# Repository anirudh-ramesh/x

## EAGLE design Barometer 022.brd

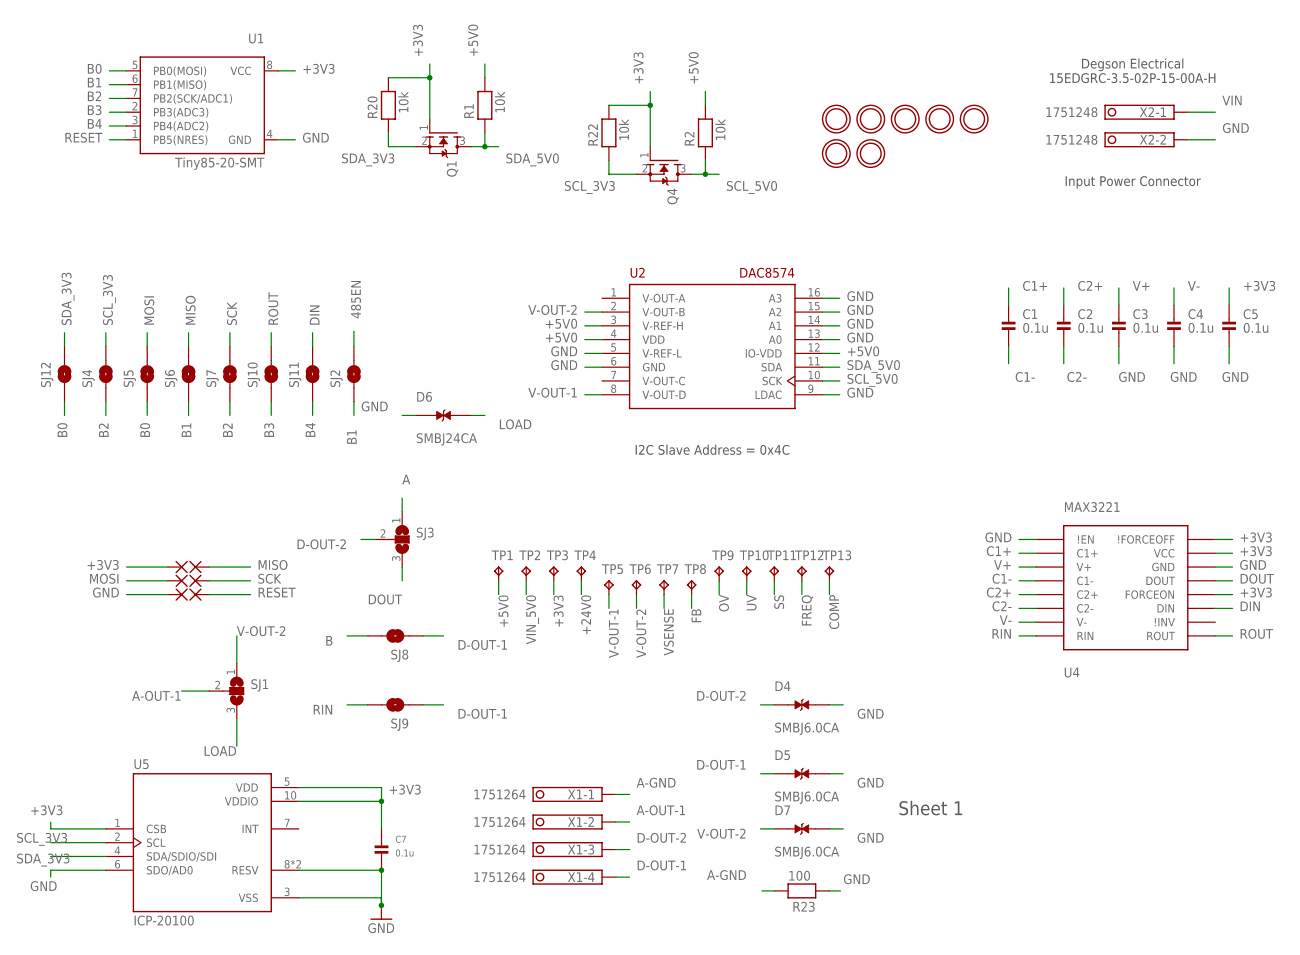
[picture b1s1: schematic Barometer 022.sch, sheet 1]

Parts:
C1, C2, C3, C4, C5, C7: 0.1u; 0603@1
D4, D5, D7: SMBJ6.0CA; DIOM4336X265N
D6: SMBJ24CA; DIOM4336X265N
PAD1, PAD2, PAD3, PAD4, PAD5, PAD6: SMD2; SMD1,27-2,54
Q1, Q4: MOSFET-NWIDE; SOT23-WIDE
R1, R2, R20, R22: 10k; 0603
R23: 100; 0603
SJ1: SJ2WW; SJ_2W
SJ2, SJ4, SJ5, SJ6, SJ7, SJ8, SJ9, SJ10, SJ11: SOLDERJUMPERTRACE; SJ_2S-TRACE
SJ3: SJ2W; SJ_2
SJ12: SOLDERJUMPERNO; SJ_2S-NO
TP1, TP2, TP3, TP4, TP5, TP6, TP7, TP8, TP9, TP10, TP11, TP12, TP13: TPB1,27; B1,27
U1: Tiny85-20-SMT; SO08-EIAJ_MCU
U2: DAC8574; TSSOP16
U4: MAX3221; TSSOP16
U5: ICP-20100; PQFN50P200X200X85-10N
U$1, U$2, U$3, U$4, U$5, U$6, U$7: MOUNTINGHOLE3.0THIN; MOUNTINGHOLE_3.0_PLATEDTHIN
X1: 1751264
X2: 1751248

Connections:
485EN: SJ2.2; also elsewhere on the board
+3V3: C5.1, C7.1, PAD1.1, Q1.1 (G), Q4.1 (G), R20.2, R22.2, TP3.TP, U1.8 (VCC), U4.12 (FORCEON), U4.15 (VCC), U4.16 (\!FORCEOFF), U5.1 (CSB), U5.5 (VDD), U5.10 (VDDIO); also elsewhere on the board
+5V0: R1.2, R2.2, TP1.TP, U2.3 (V-REF-H), U2.4 (VDD), U2.12 (IO-VDD); also elsewhere on the board
+24V0: TP4.TP; also elsewhere on the board
A: SJ3.1; also elsewhere on the board
A-GND: R23.2, X1.1
A-OUT-1: SJ1.2, X1.2
B: SJ8.2; also elsewhere on the board
B0: SJ5.1, SJ12.1, U1.5 (PB0(MOSI))
B1: SJ2.1, SJ6.1, U1.6 (PB1(MISO))
B2: SJ4.1, SJ7.1, U1.7 (PB2(SCK/ADC1))
B3: SJ10.1, U1.2 (PB3(ADC3))
B4: SJ11.1, U1.3 (PB4(ADC2))
C1+: C1.1, U4.2 (C1+)
C1-: C1.2, U4.4 (C1-)
C2+: C2.1, U4.5 (C2+)
C2-: C2.2, U4.6 (C2-)
COMP: TP13.TP; also elsewhere on the board
D-OUT-1: D5.1, SJ8.1, SJ9.1, X1.4
D-OUT-2: D4.1, SJ3.2, X1.3
DIN: SJ11.2, U4.11 (DIN); also elsewhere on the board
DOUT: SJ3.3, U4.13 (DOUT)
FB: TP8.TP; also elsewhere on the board
FREQ: TP12.TP; also elsewhere on the board
GND: C3.2, C4.2, C5.2, C7.2, D4.2, D5.2, D6.1, D7.2, PAD5.1, R23.1, U1.4 (GND), U2.5 (V-REF-L), U2.6 (GND), U2.9 (LDAC), U2.13 (A0), U2.14 (A1), U2.15 (A2), U2.16 (A3), U4.1 (\!EN), U4.14 (GND), U5.3 (VSS), U5.6 (SDO/AD0), U5.8 (RESV), U5.9 (RESV), X2.2; also elsewhere on the board
LOAD: D6.2, SJ1.3; also elsewhere on the board
MISO: PAD2.1, SJ6.2
MOSI: PAD3.1, SJ5.2
OV: TP9.TP; also elsewhere on the board
RESET: PAD6.1, U1.1 (PB5(NRES))
RIN: SJ9.2, U4.8 (RIN)
ROUT: SJ10.2, U4.9 (ROUT); also elsewhere on the board
SCK: PAD4.1, SJ7.2
SCL_3V3: Q4.2 (S), R22.1, SJ4.2, U5.2 (SCL)
SCL_5V0: Q4.3 (D), R2.1, U2.10 (SCK)
SDA_3V3: Q1.2 (S), R20.1, SJ12.2, U5.4 (SDA/SDIO/SDI)
SDA_5V0: Q1.3 (D), R1.1, U2.11 (SDA)
SS: TP11.TP; also elsewhere on the board
UV: TP10.TP; also elsewhere on the board
V+: C3.1, U4.3 (V+)
V-: C4.1, U4.7 (V-)
V-OUT-1: TP5.TP, U2.8 (V-OUT-D); also elsewhere on the board
V-OUT-2: D7.1, SJ1.1, TP6.TP, U2.2 (V-OUT-B)
VIN: X2.1; also elsewhere on the board
VIN_5V0: TP2.TP; also elsewhere on the board
VSENSE: TP7.TP; also elsewhere on the board

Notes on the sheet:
Sheet 1
I2C Slave Address = 0x4C
Input Power Connector
Degson Electrical 15EDGRC-3.5-02P-15-00A-H

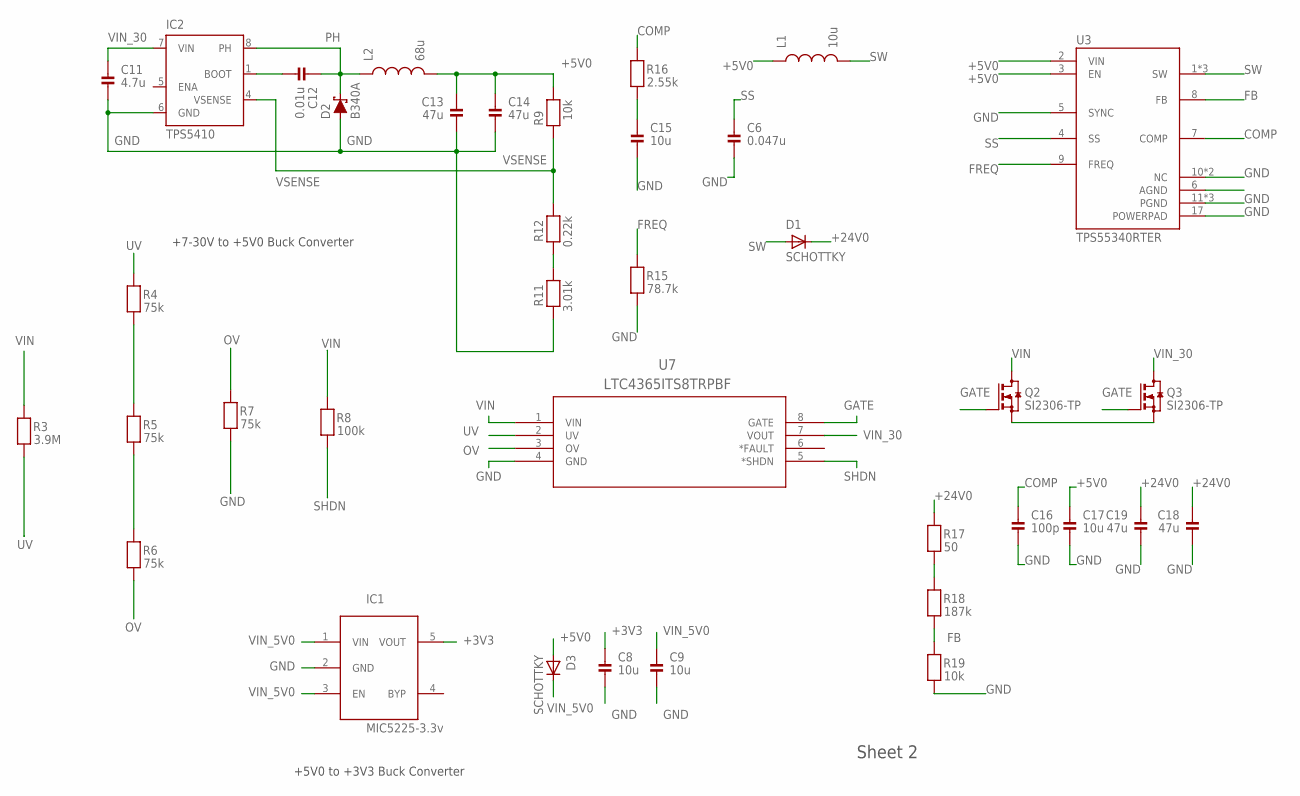
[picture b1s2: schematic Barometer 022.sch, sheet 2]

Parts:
C6: 0.047u; 0603@1
C8, C9, C15, C17: 10u; 0603@1
C11: 4.7u; 0805@1
C12: 0.01u; 0603@1
C13, C14, C18, C19: 47u; 1206@1
C16: 100p; 0603@1
D1, D3: SCHOTTKY; SOD-123FL
D2: B340A; SMA-DIODE
IC1: MIC5225-3.3v; SOT23-5L
IC2: TPS5410; D_R-PDSO-G08
L1: 10u; VLS6045EX
L2: 68u; VLS6045EX
Q2, Q3: SI2306-TP; SOT23
R3: 3.9M; 0603
R4, R5, R6, R7: 75k; 0603
R8: 100k; 0603
R9, R19: 10k; 0603
R11: 3.01k; 0603
R12: 0.22k; 0603
R15: 78.7k; 0603
R16: 2.55k; 0603
R17: 50; 0603
R18: 187k; 0603
U3: TPS55340RTER; QFN50P300X300X80-17N
U7: LTC4365ITS8TRPBF; TSOT-23_TS8

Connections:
+3V3: C8.1, IC1.5 (VOUT); also elsewhere on the board
+5V0: C13.1, C14.1, C17.1, D3.A, L1.1, L2.2, R9.2, U3.2 (VIN), U3.3 (EN); also elsewhere on the board
+24V0: C18.1, C19.1, D1.C, R17.2; also elsewhere on the board
BOOT1: C12.2, IC2.1 (BOOT)
COMP: C16.1, R16.2, U3.7 (COMP); also elsewhere on the board
FB: R18.1, R19.2, U3.8 (FB); also elsewhere on the board
FREQ: R15.2, U3.9 (FREQ); also elsewhere on the board
GATE: Q2.1 (G), Q3.1 (G), U7.8 (GATE)
GND: C6.2, C8.2, C9.2, C11.2, C13.2, C14.2, C15.2, C16.2, C17.2, C18.2, C19.2, D2.A, IC1.2 (GND), IC2.6 (GND), R7.1, R11.1, R15.1, R19.1, U3.5 (SYNC), U3.10 (NC), U3.11 (PGND), U3.12 (PGND), U3.13 (PGND), U3.14 (NC), U3.17 (POWERPAD), U7.4 (GND); also elsewhere on the board
unnamed: C15.1, R16.1
unnamed: R4.1, R5.2
unnamed: Q2.2 (S), Q3.2 (S)
unnamed: R5.1, R6.2
unnamed: R11.2, R12.1
unnamed: R17.1, R18.2
OV: R6.1, R7.2, U7.3 (OV); also elsewhere on the board
PH: C12.1, D2.C, IC2.8 (PH), L2.1
SHDN: R8.1, U7.5 (*SHDN)
SS: C6.1, U3.4 (SS); also elsewhere on the board
SW: D1.A, L1.2, U3.1 (SW), U3.15 (SW), U3.16 (SW)
UV: R3.1, R4.2, U7.2 (UV); also elsewhere on the board
VIN: Q2.3 (D), R3.2, R8.2, U7.1 (VIN); also elsewhere on the board
VIN_5V0: C9.1, D3.C, IC1.1 (VIN), IC1.3 (EN); also elsewhere on the board
VIN_30: C11.1, IC2.7 (VIN), Q3.3 (D), U7.7 (VOUT)
VSENSE: IC2.4 (VSENSE), R9.1, R12.2; also elsewhere on the board

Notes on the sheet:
Sheet 2
+7-30V to +5V0 Buck Converter
+5V0 to +3V3 Buck Converter

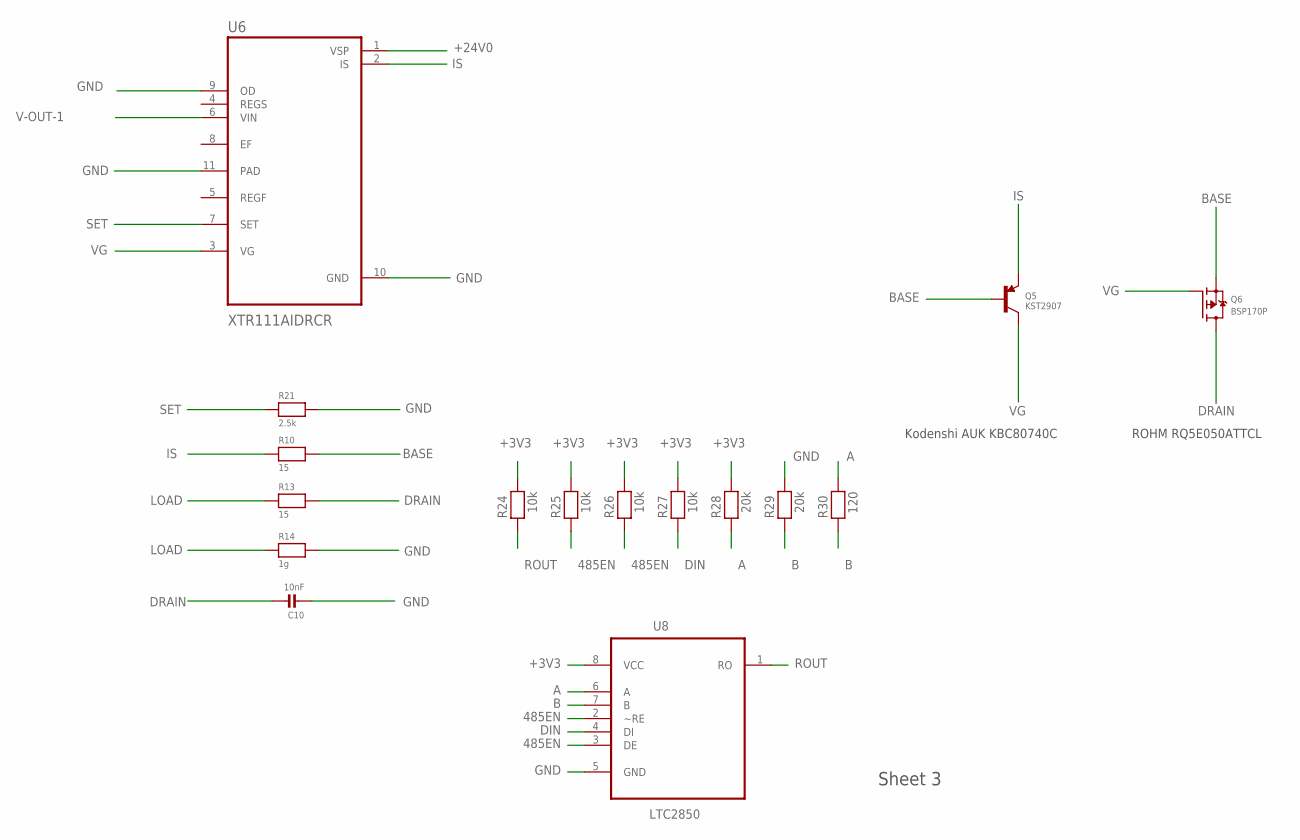
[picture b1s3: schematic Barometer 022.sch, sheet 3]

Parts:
C10: 10nF; 0603@1
Q5: KST2907; SOT23-R
Q6: BSP170P; SOT23-R
R10, R13: 15; 0603
R14: 1g; 0603
R21: 2.5k; 0603
R24, R25, R26, R27: 10k; 0603
R28, R29: 20k; 0603
R30: 120; 0603
U6: XTR111AIDRCR; VREG_V62/16624-01YE
U8: LTC2850; SOIC127P600X175-8N

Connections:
485EN: R25.1, R26.1, U8.2 (~RE), U8.3 (DE); also elsewhere on the board
+3V3: R24.2, R25.2, R26.2, R27.2, R28.2, U8.8 (VCC); also elsewhere on the board
+24V0: U6.1 (VSP); also elsewhere on the board
A: R28.1, R30.2, U8.6 (A); also elsewhere on the board
B: R29.1, R30.1, U8.7 (B); also elsewhere on the board
BASE: Q5.1 (B), Q6.2 (S), R10.2
DIN: R27.1, U8.4 (DI); also elsewhere on the board
DRAIN: C10.2, Q6.3 (D), R13.2
GND: C10.1, R14.2, R21.2, R29.2, U6.9 (OD), U6.10 (GND), U6.11 (PAD), U8.5 (GND); also elsewhere on the board
IS: Q5.2 (E), R10.1, U6.2 (IS)
LOAD: R13.1, R14.1; also elsewhere on the board
ROUT: R24.1, U8.1 (RO); also elsewhere on the board
SET: R21.1, U6.7 (SET)
V-OUT-1: U6.6 (VIN); also elsewhere on the board
VG: Q5.3 (C), Q6.1 (G), U6.3 (VG)

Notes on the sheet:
Sheet 3
ROHM RQ5E050ATTCL
Kodenshi AUK KBC80740C

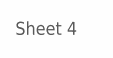
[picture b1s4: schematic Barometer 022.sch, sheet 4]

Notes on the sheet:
Sheet 4

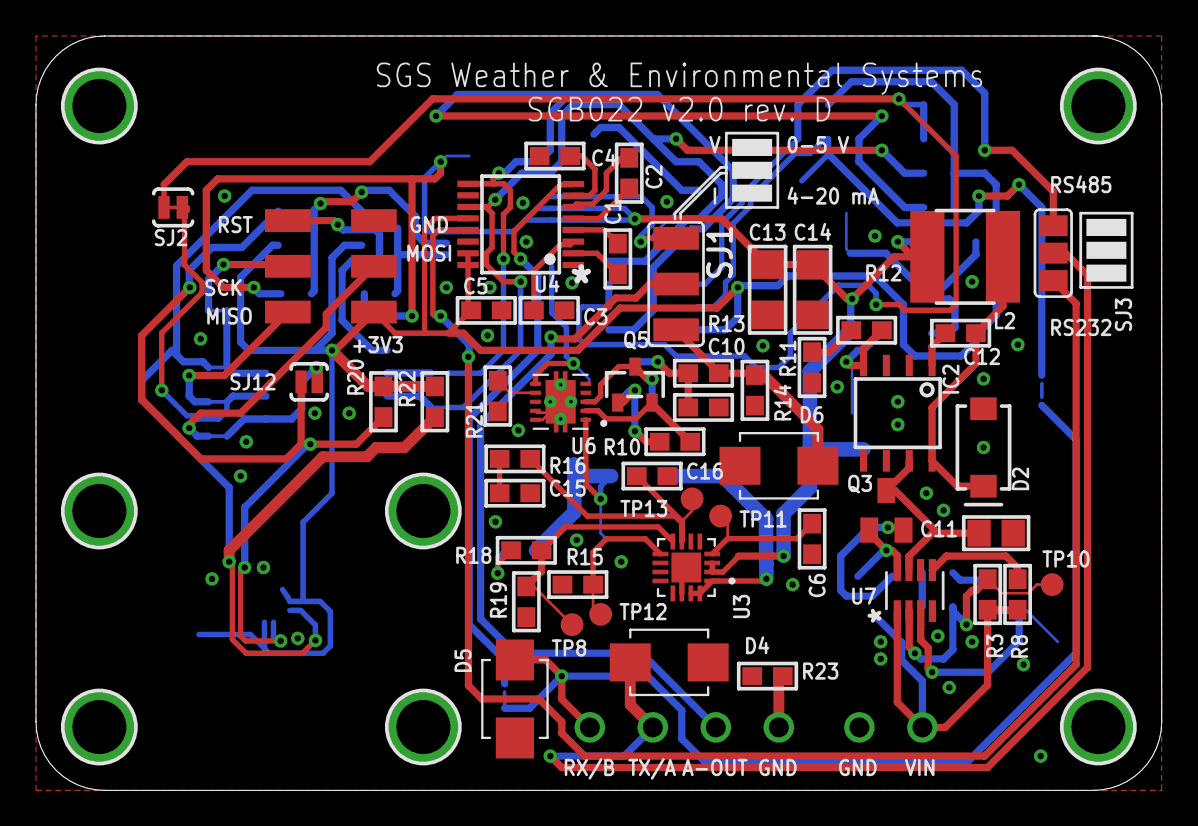
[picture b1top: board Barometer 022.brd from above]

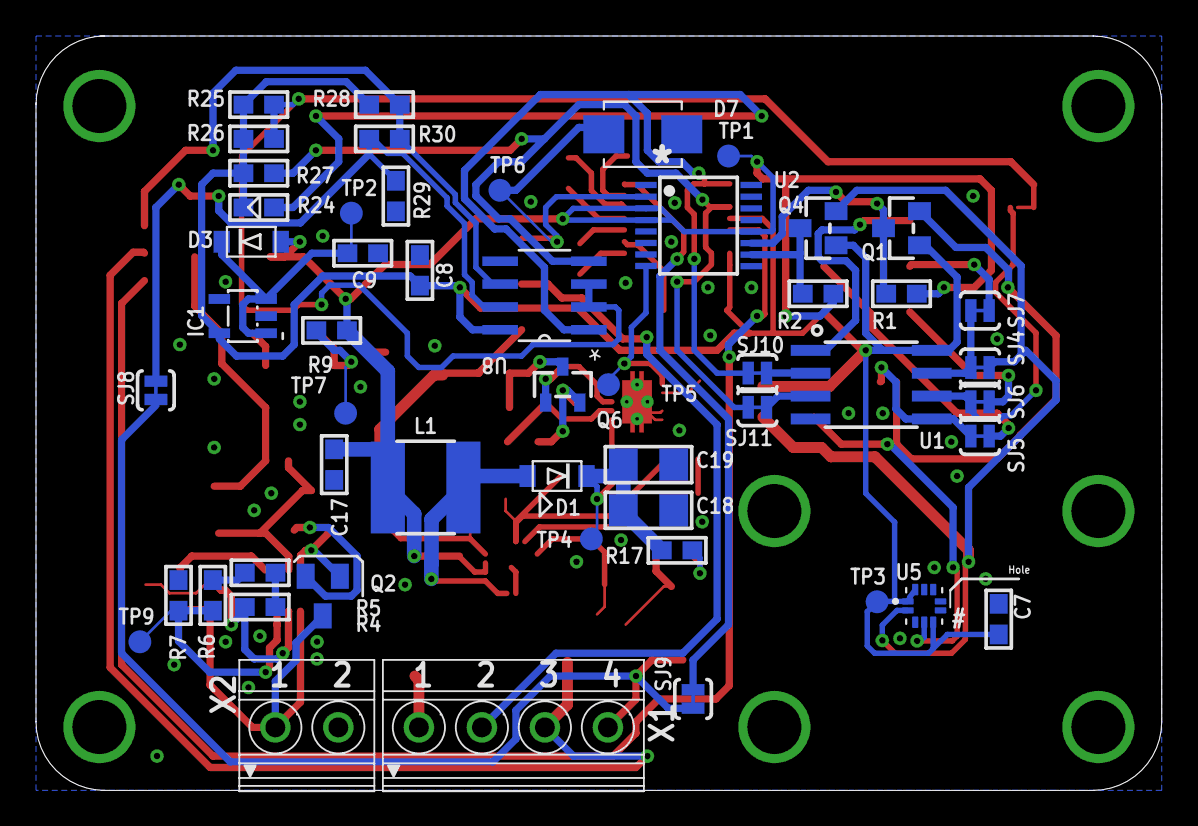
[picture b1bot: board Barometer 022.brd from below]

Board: 2 copper layers, 62.5 x 41.9 mm, 114 parts (52 on the bottom side), 63 nets.

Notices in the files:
parts and their libraries:
SparkFun-Retired-0: Licensing: Creative Commons ShareAlike 4.0 International - https://creativecommons.org/licenses/by-sa/4.0
microbuilder: This work is placed in the public domain, and may be freely used for commercial and non-commercial work with the following conditions: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
